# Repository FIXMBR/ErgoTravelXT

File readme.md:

## ErgoTravelXT

Portable, low profile keyboard with extra XT60s.

Based on original ErgoTravel by jpconstantineau [here](https://github.com/jpconstantineau/ErgoTravel)

Changes from the original ErgoTravel.

- Kalih Choc switches only (no MX switches)
- Tighter key grid (only 17.5x16.5mm Kalih keycaps supported)
- Removed LEDs because I was lazy
- One extra key
- **10 XT60 connectors**
- Foldable
- Connectable (if you connect the two halves you don't need TRRS cable)

## Build

**See issues below.**

Build process is pretty similiar to [original ErgoTravel](https://github.com/jpconstantineau/ErgoTravel/blob/master/BuildInstructions.md).

Also please use I2C, it's based.

You will need three pairs of standard XT60s and two pairs of right angle XT60s (XT60PW).
Before soldering them you will probably have to cut those metal contacts in half, without doing that, they won't fit.

The "case" consists of a 3d printed top plate (available in 3Dmodels directory), and an extra PCB, that you solder at the end **after testing everything**. Disassembly can be really difficult, you don't want to deal with that.
As the minimal order quantity from JLCPCB is 5pcs it's enough for two actual PCBs and two bottom plates, with one pcb extra.
When it comes to soldering the bottom plates, I soldered them in the place where XT60s are and in the middle of the board for extra rigidity.

## Issues

3D printed case I used turned out to be a bit too tight and the keyboard ended up being a bit banana-like, due to insufficient tolerances. In the file in this repo I added extra spacing, so it **should** be fine, but if you see that the top plate with switches inserted in it bends, add more spacing and re-print.

Using a PCB as a keyboard case/bottom plate is risky because you can create a short by placing it on something conductive. You should add some rubber feet and preferably add a conformal coating to the board (and desoldering it will be a pain.)

Also no Arch Linux logo in the included files, I don't want to deal with copyright

## Code

Code folder includes modified ErgoTravel qmk firmware. It supports the extra key, thats on the ErgoTravelXT.

## Photos

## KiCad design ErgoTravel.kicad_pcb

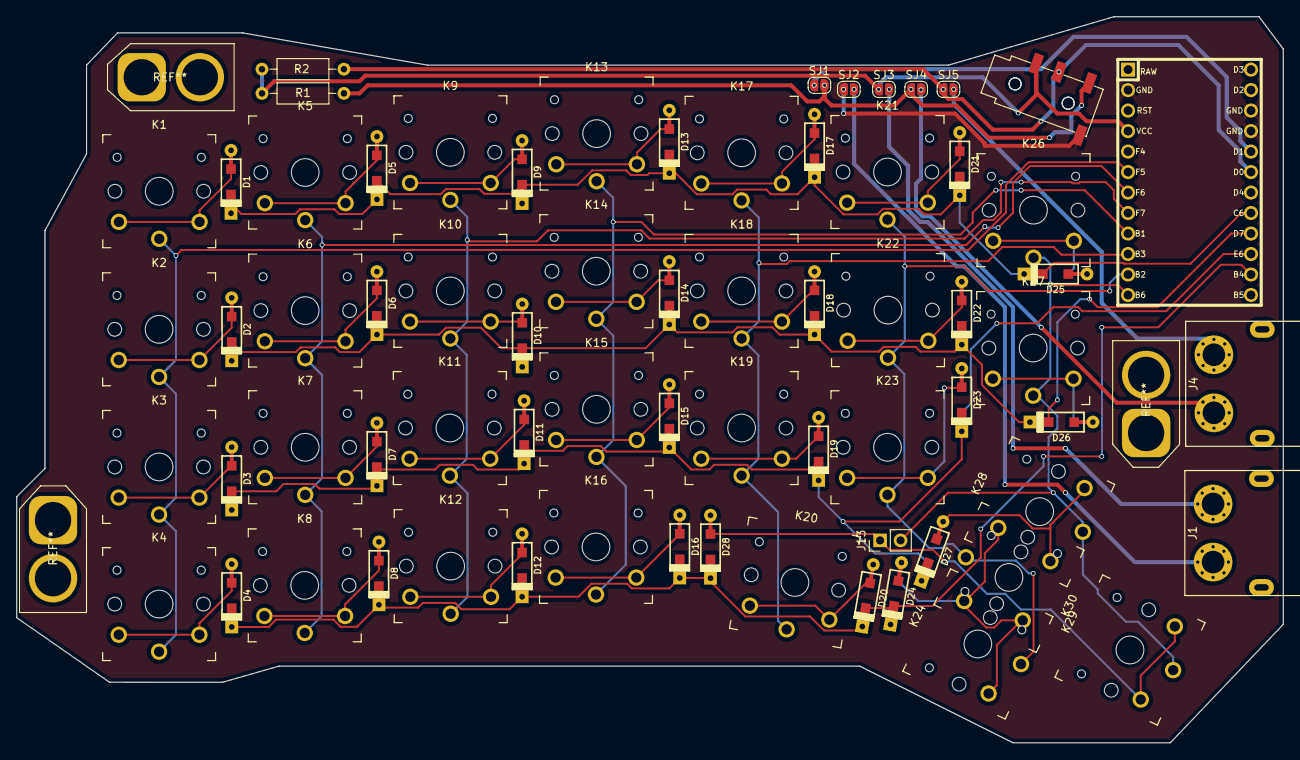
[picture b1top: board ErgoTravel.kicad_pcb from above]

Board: 2 copper layers, 157.0 x 90.0 mm, 70 parts (1 on the bottom side), 48 nets.

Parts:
D1, D2, D3, D4, D5, D6, D7, D8, D9, D10, D11, D12, D13, D14, D15, D16, D17, D18, D19, D20, D21, D22, D23, D24, D25, D26, D27, D28: D; D_SOD123_axial-dual
J1, J4: Conn_01x02; XT60PW
J2, J3: Audio-Jack-4; PJ320D_3.5mm_Jack
J13: Conn_01x02; Pin_Header_Straight_1x02_Pitch2.54mm
K1, K2, K3, K4, K5, K6, K7, K8, K9, K10, K11, K12, K13, K14, K15, K16, K17, K18, K19, K20, K21, K22, K23, K24, K26, K27, K28, K29, K30: KEYSW; SW_PG1350_reversible
R1, R2: 4.7k; R_Axial_DIN0207_L6.3mm_D2.5mm_P10.16mm_Horizontal
SJ1, SJ2, SJ3, SJ4, SJ5: SOLDER_JUMPER; SolderJumper-Double-2_P1.3mm_Open_RoundedPad1.0x1.5mm
U1: ProMicro; Pro_Micro

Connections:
GND: J2.4, J3.4, SJ2.1, U1.2 (GND), U1.15 (GND), U1.16 (GND)
MISO: K17.1, K18.1, K19.1, K20.1, U1.10 (PB3)
MOSI: K21.1, K22.1, K23.1, K24.1, K30.1, U1.11 (PB2)
unnamed: D1.2 (A), K1.2
unnamed: D2.2 (A), K2.2
unnamed: D3.2 (A), K3.2
unnamed: D4.2 (A), K4.2
unnamed: D5.2 (A), K5.2
unnamed: D6.2 (A), K6.2
unnamed: D7.2 (A), K7.2
unnamed: D8.2 (A), K8.2
unnamed: D9.2 (A), K9.2
unnamed: D10.2 (A), K10.2
unnamed: D11.2 (A), K11.2
unnamed: D12.2 (A), K12.2
unnamed: D13.2 (A), K13.2
unnamed: D14.2 (A), K14.2
unnamed: D15.2 (A), K15.2
unnamed: D16.2 (A), K16.2
unnamed: D17.2 (A), K17.2
unnamed: D18.2 (A), K18.2
unnamed: D19.2 (A), K19.2
unnamed: D20.2 (A), K20.2
unnamed: D21.2 (A), K21.2
unnamed: D22.2 (A), K22.2
unnamed: D23.2 (A), K23.2
unnamed: D24.2 (A), K24.2, K30.2
unnamed: D25.2 (A), K26.2
unnamed: D26.2 (A), K27.2
unnamed: D27.2 (A), K28.2
unnamed: D28.2 (A), J13.1, K29.2
unnamed: J1.1, SJ2.2
unnamed: J1.2, SJ3.2
unnamed: J4.1, SJ4.2
unnamed: J4.2, SJ5.2
SCK: K13.1, K14.1, K15.1, K16.1, U1.9 (PB1)
VCC: J2.3, J3.3, R1.1, R2.1, SJ3.1, U1.4 (VCC)
col0: K1.1, K2.1, K3.1, K4.1, U1.6 (PF5)
col1: K5.1, K6.1, K7.1, K8.1, U1.7 (PF6)
col2: K9.1, K10.1, K11.1, K12.1, U1.8 (PF7)
col6: J13.2, K26.1, K27.1, K28.1, K29.1, U1.12 (PB6)
row0: D1.1 (K), D5.1 (K), D9.1 (K), D13.1 (K), D17.1 (K), D21.1 (K), D25.1 (K), U1.20 (PC6)
row1: D2.1 (K), D6.1 (K), D10.1 (K), D14.1 (K), D18.1 (K), D22.1 (K), D26.1 (K), U1.21 (PD7)
row2: D3.1 (K), D7.1 (K), D11.1 (K), D15.1 (K), D19.1 (K), D23.1 (K), D27.1 (K), U1.22 (PE6)
row3: D4.1 (K), D8.1 (K), D12.1 (K), D16.1 (K), D20.1 (K), D24.1 (K), D28.1 (K), U1.23 (PB4)
scl: J2.2, J3.2, R2.2, SJ5.1, U1.18 (PD0)
sda: J2.1, J3.1, R1.2, SJ1.2, SJ4.1
sdaPM: SJ1.1, U1.17 (PD1)

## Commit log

2022-04-18 Create LICENSE
2022-04-19 more photos
2022-04-20 Create Sjenica1
    Authorized mit meine Account Sjenica1 github.com reufrujevic750@gmail.com
